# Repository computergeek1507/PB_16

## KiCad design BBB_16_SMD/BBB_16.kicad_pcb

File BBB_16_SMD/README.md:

# Copyright and Disclaimer
Copyright: Scott Hanson

This documentation describes Open Hardware and is licensed under the CERN Open Hardware License Version 2 - Strongly Reciprocal. (CERN-OHL-S)

You may redistribute and modify this documentation under the terms of the CERN OHL-S-v2 (https://ohwr.org/cern_ohl_s_v2.txt). This documentation is distributed WITHOUT ANY EXPRESS OR IMPLIED WARRANTY, INCLUDING OF MERCHANTABILITY, SATISFACTORY QUALITY AND FITNESS FOR A PARTICULAR PURPOSE. Please see the CERN OHL v2-S for applicable conditions

**Under CERN OHL-S-v2, derivative work must be publicly released as defined in subsection 3.3**

# BBB 16 SMD

**WIP** Proceed at your own risk.

The BBB 16 SMD is a Surface Mount(SMD) BeagleBone Version with 16 pixel ports, 1 remote differential port, 2 serial ports, and an expansion header for additional 16 pixel outputs. Uses Falcon v4 (24 pin) Expansion Pinout.

**Warning** Due to part shortages, I have switched this design(v3) to use 3.81mm Phoenix Connectors for the string ports. Most other controllers (Falcon, Kulps) use 3.50mm Phoenix Connectors and the plugs are not compatible. The PCB footprints can accept both 3.81mm and 3.50mm headers, but the parts in the BOM are 3.81mm at the moment. 

To order PCBs upload the ["GERBER-BBB_16.zip"](https://github.com/computergeek1507/PB_16/raw/master/BBB_16_SMD/jlcpcb/gerber/GERBER-BBB_16.zip) file in the "jlcpcb\gerber" folder to jlcpcb.com. Enable the SMD service, 'BOM-BBB_16.csv' is the SMD BOM and 'POS-BBB_16.csv' is the SMD CPL position file.

## [Interactive BOM](https://computergeek1507.github.io/PB_16/BBB_16_SMD/bom/ibom)

## [Part BOM](https://github.com/computergeek1507/PB_16/raw/master/BBB_16_SMD/BBB_16_BOM.ods)

---
## Changelog

v2.1
-
* Switched String Ports to 3.81mm Phoenix Connectors.
* Switched Serial Ports AM26C31 serial chip, same as differential port.
* Updated 5V regulator to "Universal" footprint to support different regulators.

v2
-
* first SMD version.

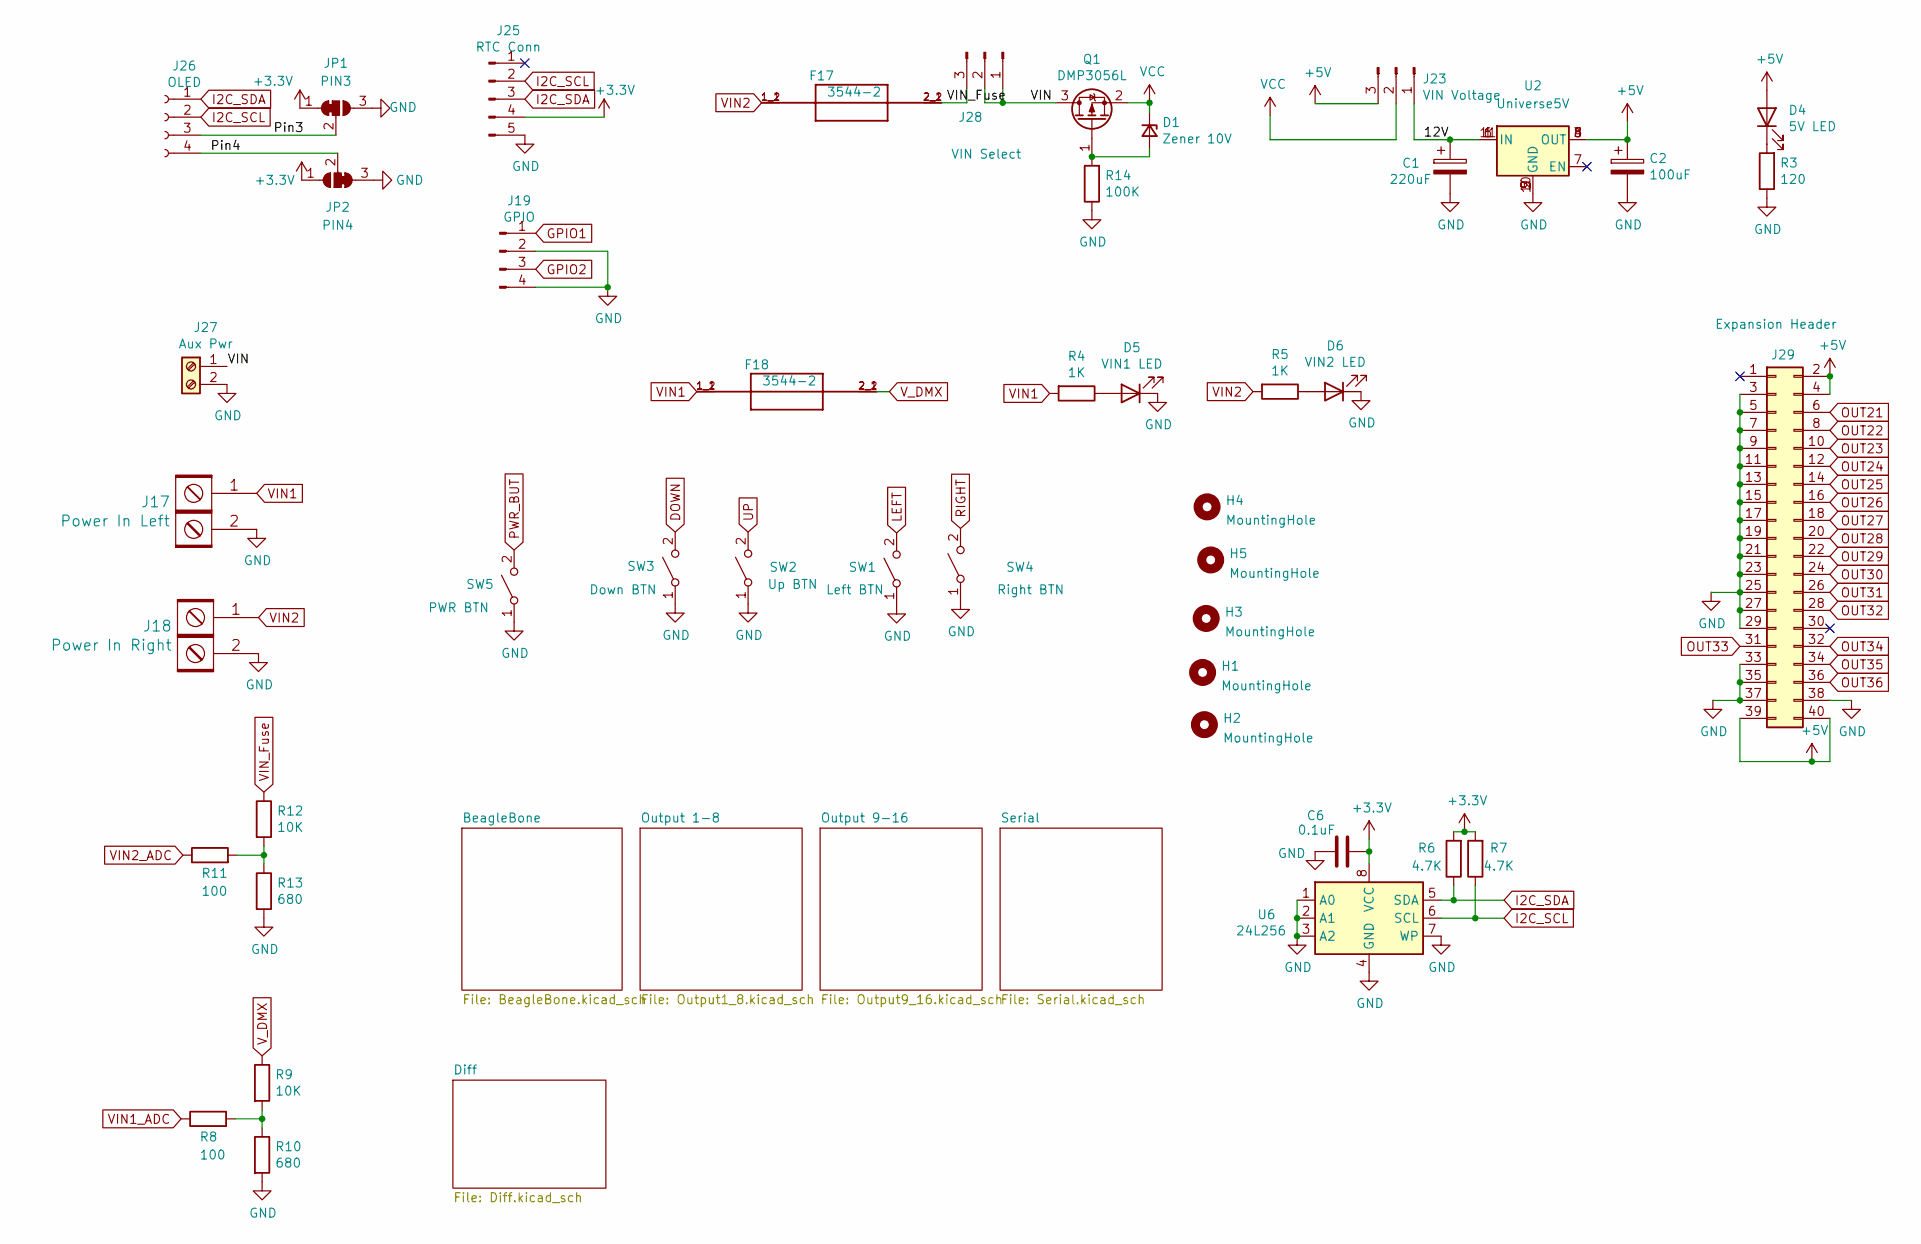
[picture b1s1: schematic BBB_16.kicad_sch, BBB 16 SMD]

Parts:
C1: 220uF; CP_Radial_D10.0mm_P5.00mm; MPN ECA-1HM221; Digi-Key_PN P5183-ND
C2: 100uF; CP_Elec_6.3x5.4_Nichicon; MPN UWX1C101MCL1GB; Digi-Key_PN 493-2105-1-ND
C6: 0.1uF; C_0603_1608Metric_Pad1.08x0.95mm_HandSolder; MPN CL10B104KB8NNWC; Digi-Key_PN 1276-1935-2-ND
D1: Zener 10V; D_SOD-123; MPN MMSZ5240B-7-F; Digi-Key_PN MMSZ5240B-FDICT-ND
D4: 5V LED; LED_0603_1608Metric_Pad1.05x0.95mm_HandSolder; MPN LTST-C190KRKT; Digi-Key_PN 160-1436-2-ND
D5: VIN1 LED; LED_0603_1608Metric_Pad1.05x0.95mm_HandSolder; MPN LTST-C190KRKT; Digi-Key_PN 160-1436-2-ND
D6: VIN2 LED; LED_0603_1608Metric_Pad1.05x0.95mm_HandSolder; MPN LTST-C190KRKT; Digi-Key_PN 160-1436-2-ND
F17, F18: 3544-2; FUSE_3544-2; MPN 3544-2; Digi-Key_PN 36-3544-2-ND
H1, H2, H3, H4, H5: MountingHole; MountingHole_3.7mm
J17: Power In Left; BARRIER_BLOCK_1ROW_2POS_P9.5MM; MPN OSTYK51102030; Digi-Key_PN ED2953-ND
J18: Power In Right; BARRIER_BLOCK_1ROW_2POS_P9.5MM; MPN OSTYK51102030; Digi-Key_PN ED2953-ND
J19: GPIO; JST_XH_B4B-XH-A_1x04_P2.50mm_Vertical; MPN B4B-XH-A(LF)(SN); Digi-Key_PN 455-2249-ND
J23: VIN Voltage; PinHeader_1x03_P2.54mm_Vertical; MPN 61300311121; Digi-Key_PN 732-5316-ND
J25: RTC Conn; PinHeader_1x05_P2.54mm_Vertical; MPN 61300511121; Digi-Key_PN 732-5318-ND
J26: OLED; OLED-SSD1306-128X64-I2C-THT_2HOLE; MPN PPTC041LFBN-RC; Digi-Key_PN S7002-ND
J27: Aux Pwr; PHOENIX_MKDS1_2-3.81; MPN 1727010; Digi-Key_PN 277-1947-ND
J28: VIN Select; PinHeader_1x03_P2.54mm_Vertical; MPN 61300311121; Digi-Key_PN 732-5316-ND
J29: Expansion Header; IDC-Header_2x20_P2.54mm_Vertical; MPN SBH11-PBPC-D20-ST-BK; Digi-Key_PN S9175-ND
JP1: PIN3; SolderJumper-3_P1mm_Bridged12
JP2: PIN4; SolderJumper-3_P1mm_Bridged23
Q1: DMP3056L; SOT-23; MPN DMP3056L-7; Digi-Key_PN DMP3056L-7DICT-ND
R3: 120; R_0603_1608Metric_Pad0.98x0.95mm_HandSolder; MPN CRGCQ0603F120R; Digi-Key_PN A129677CT-ND
R4, R5: 1K; R_0603_1608Metric_Pad0.98x0.95mm_HandSolder; MPN RC0603FR-071KL; Digi-Key_PN 311-1.00KHRTR-ND
R6, R7: 4.7K; R_0603_1608Metric_Pad0.98x0.95mm_HandSolder; MPN RC0603JR-074K7L; Digi-Key_PN 311-4.7KGRCT-ND
R8, R11: 100; R_0603_1608Metric_Pad0.98x0.95mm_HandSolder; MPN RMCF0603FT100R; Digi-Key_PN RMCF0603FT100RCT-ND
R9, R12: 10K; R_0603_1608Metric_Pad0.98x0.95mm_HandSolder; MPN RC0603FR-0710KL; Digi-Key_PN 311-10.0KHRCT-ND
R10, R13: 680; R_0603_1608Metric_Pad0.98x0.95mm_HandSolder; MPN RC0603FR-07680RL; Digi-Key_PN 311-680HRCT-ND
R14: 100K; R_0603_1608Metric_Pad0.98x0.95mm_HandSolder; MPN RT0603BRD07100KL; Digi-Key_PN YAG1235CT-ND
SW1: Left BTN; SW_Push_1P1T_NO_6x6mm_H9.5mm; MPN PTS645SL50SMTR92 LFS; Digi-Key_PN CKN9088CT-ND
SW2: Up BTN; SW_Push_1P1T_NO_6x6mm_H9.5mm; MPN PTS645SL50SMTR92 LFS; Digi-Key_PN CKN9088CT-ND
SW3: Down BTN; SW_Push_1P1T_NO_6x6mm_H9.5mm; MPN PTS645SL50SMTR92 LFS; Digi-Key_PN CKN9088CT-ND
SW4: Right BTN; SW_Push_1P1T_NO_6x6mm_H9.5mm; MPN PTS645SL50SMTR92 LFS; Digi-Key_PN CKN9088CT-ND
SW5: PWR BTN; SW_Push_1P1T_NO_6x6mm_H9.5mm; MPN PTS645SL50SMTR92 LFS; Digi-Key_PN CKN9088CT-ND
U2: Universe5V; Universal_5V_Horizontal
U6: 24L256; SOIC-8_3.9x4.9mm_P1.27mm; MPN 24LC256T-I/MS; Digi-Key_PN 24LC256T-I/MSCT-ND

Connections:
+3V3: C6.1, J25.4, JP1.1 (A), JP2.1 (A), R6.2, R7.2, U6.8 (VCC); also elsewhere on the board
+5V: C2.1, D4.2 (A), J23.3, J29.2, J29.4, J29.39, J29.40, U2.3 (OUT), U2.4 (OUT), U2.8 (OUT); also elsewhere on the board
/12V: C1.1, J23.1, U2.1 (IN), U2.6 (IN), U2.11 (IN)
/Pin3: J26.3, JP1.2 (C)
/Pin4: J26.4, JP2.2 (C)
/VIN: J27.1, J28.1, J28.2, Q1.3 (D)
DOWN: SW3.2 (B); also elsewhere on the board
GND: C1.2, C2.2, C6.2, D5.1 (K), D6.1 (K), J17.2, J18.2, J19.2, J19.4, J25.5, J27.2, J29.3, J29.5, J29.7, J29.9, J29.11, J29.13, J29.15, J29.17, J29.19, J29.21, J29.23, J29.25, J29.27, J29.29, J29.33, J29.35, J29.37, J29.38, JP1.3 (B), JP2.3 (B), R3.1, R10.2, R13.2, R14.1, SW1.1 (A), SW2.1 (A), SW3.1 (A), SW4.1 (A), SW5.1 (A), U2.2 (GND), U2.5 (GND), U2.9 (GND), U2.10 (GND), U6.1 (A0), U6.2 (A1), U6.3 (A2), U6.4 (GND), U6.7 (WP); also elsewhere on the board
GPIO1: J19.1; also elsewhere on the board
GPIO2: J19.3; also elsewhere on the board
I2C_SCL: J25.2, J26.2, R7.1, U6.6 (SCL); also elsewhere on the board
I2C_SDA: J25.3, J26.1, R6.1, U6.5 (SDA); also elsewhere on the board
LEFT: SW1.2 (B); also elsewhere on the board
unnamed: D1.2 (A), Q1.1 (G), R14.2
unnamed: D4.1 (K), R3.2
unnamed: D5.2 (A), R4.1
unnamed: D6.2 (A), R5.1
unnamed: R8.2, R9.2, R10.1
unnamed: R11.2, R12.2, R13.1
OUT21: J29.6; also elsewhere on the board
OUT22: J29.8; also elsewhere on the board
OUT23: J29.10; also elsewhere on the board
OUT24: J29.12; also elsewhere on the board
OUT25: J29.14; also elsewhere on the board
OUT26: J29.16; also elsewhere on the board
OUT27: J29.18; also elsewhere on the board
OUT28: J29.20; also elsewhere on the board
OUT29: J29.22; also elsewhere on the board
OUT30: J29.24; also elsewhere on the board
OUT31: J29.26; also elsewhere on the board
OUT32: J29.28; also elsewhere on the board
OUT33: J29.31; also elsewhere on the board
OUT34: J29.32; also elsewhere on the board
OUT35: J29.34; also elsewhere on the board
OUT36: J29.36; also elsewhere on the board
PWR_BUT: SW5.2 (B); also elsewhere on the board
RIGHT: SW4.2 (B); also elsewhere on the board
UP: SW2.2 (B); also elsewhere on the board
VCC: D1.1 (K), J23.2, Q1.2 (S)
VIN1: F18.1_1 (1), F18.1_2 (1), J17.1, R4.2; also elsewhere on the board
VIN1_ADC: R8.1; also elsewhere on the board
VIN2: F17.1_1 (1), F17.1_2 (1), J18.1, R5.2; also elsewhere on the board
VIN2_ADC: R11.1; also elsewhere on the board
VIN_Fuse: F17.2_1 (2), F17.2_2 (2), J28.3, R12.1
V_DMX: F18.2_1 (2), F18.2_2 (2), R9.1; also elsewhere on the board

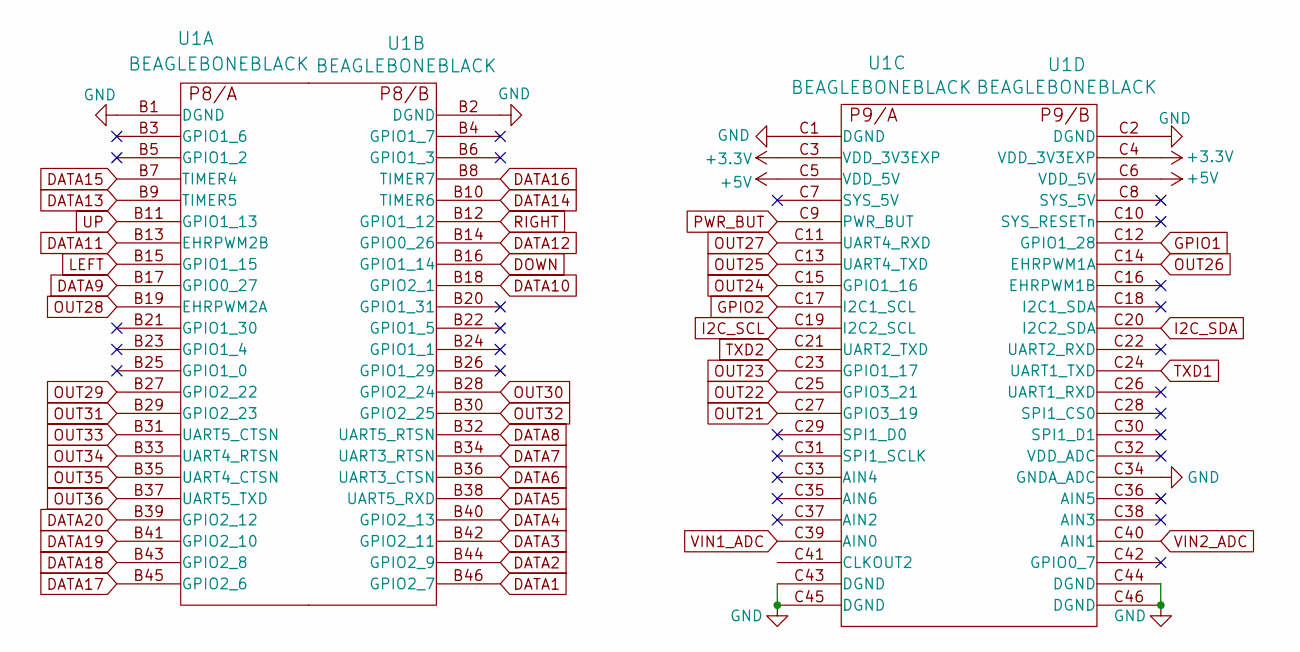
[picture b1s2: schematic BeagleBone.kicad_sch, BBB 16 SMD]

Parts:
U1: BEAGLEBONEBLACK; MPN BBB01-SC-505; Digi-Key_PN BBB01-SC-505-ND

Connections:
+3V3: U1.C3 (VDD_3V3EXP), U1.C4 (VDD_3V3EXP); also elsewhere on the board
+5V: U1.C5 (VDD_5V), U1.C6 (VDD_5V); also elsewhere on the board
DATA1: U1.B46 (GPIO2_7); also elsewhere on the board
DATA2: U1.B44 (GPIO2_9); also elsewhere on the board
DATA3: U1.B42 (GPIO2_11); also elsewhere on the board
DATA4: U1.B40 (GPIO2_13); also elsewhere on the board
DATA5: U1.B38 (UART5_RXD); also elsewhere on the board
DATA6: U1.B36 (UART3_CTSN); also elsewhere on the board
DATA7: U1.B34 (UART3_RTSN); also elsewhere on the board
DATA8: U1.B32 (UART5_RTSN); also elsewhere on the board
DATA9: U1.B17 (GPIO0_27); also elsewhere on the board
DATA10: U1.B18 (GPIO2_1); also elsewhere on the board
DATA11: U1.B13 (EHRPWM2B); also elsewhere on the board
DATA12: U1.B14 (GPIO0_26); also elsewhere on the board
DATA13: U1.B9 (TIMER5); also elsewhere on the board
DATA14: U1.B10 (TIMER6); also elsewhere on the board
DATA15: U1.B7 (TIMER4); also elsewhere on the board
DATA16: U1.B8 (TIMER7); also elsewhere on the board
DATA17: U1.B45 (GPIO2_6); also elsewhere on the board
DATA18: U1.B43 (GPIO2_8); also elsewhere on the board
DATA19: U1.B41 (GPIO2_10); also elsewhere on the board
DATA20: U1.B39 (GPIO2_12); also elsewhere on the board
DOWN: U1.B16 (GPIO1_14); also elsewhere on the board
GND: U1.B1 (DGND), U1.B2 (DGND), U1.C1 (DGND), U1.C2 (DGND), U1.C34 (GNDA_ADC), U1.C43 (DGND), U1.C44 (DGND), U1.C45 (DGND), U1.C46 (DGND); also elsewhere on the board
GPIO1: U1.C12 (GPIO1_28); also elsewhere on the board
GPIO2: U1.C17 (I2C1_SCL); also elsewhere on the board
I2C_SCL: U1.C19 (I2C2_SCL); also elsewhere on the board
I2C_SDA: U1.C20 (I2C2_SDA); also elsewhere on the board
LEFT: U1.B15 (GPIO1_15); also elsewhere on the board
OUT21: U1.C27 (GPIO3_19); also elsewhere on the board
OUT22: U1.C25 (GPIO3_21); also elsewhere on the board
OUT23: U1.C23 (GPIO1_17); also elsewhere on the board
OUT24: U1.C15 (GPIO1_16); also elsewhere on the board
OUT25: U1.C13 (UART4_TXD); also elsewhere on the board
OUT26: U1.C14 (EHRPWM1A); also elsewhere on the board
OUT27: U1.C11 (UART4_RXD); also elsewhere on the board
OUT28: U1.B19 (EHRPWM2A); also elsewhere on the board
OUT29: U1.B27 (GPIO2_22); also elsewhere on the board
OUT30: U1.B28 (GPIO2_24); also elsewhere on the board
OUT31: U1.B29 (GPIO2_23); also elsewhere on the board
OUT32: U1.B30 (GPIO2_25); also elsewhere on the board
OUT33: U1.B31 (UART5_CTSN); also elsewhere on the board
OUT34: U1.B33 (UART4_RTSN); also elsewhere on the board
OUT35: U1.B35 (UART4_CTSN); also elsewhere on the board
OUT36: U1.B37 (UART5_TXD); also elsewhere on the board
PWR_BUT: U1.C9 (PWR_BUT); also elsewhere on the board
RIGHT: U1.B12 (GPIO1_12); also elsewhere on the board
TXD1: U1.C24 (UART1_TXD); also elsewhere on the board
TXD2: U1.C21 (UART2_TXD); also elsewhere on the board
UP: U1.B11 (GPIO1_13); also elsewhere on the board
VIN1_ADC: U1.C39 (AIN0); also elsewhere on the board
VIN2_ADC: U1.C40 (AIN1); also elsewhere on the board

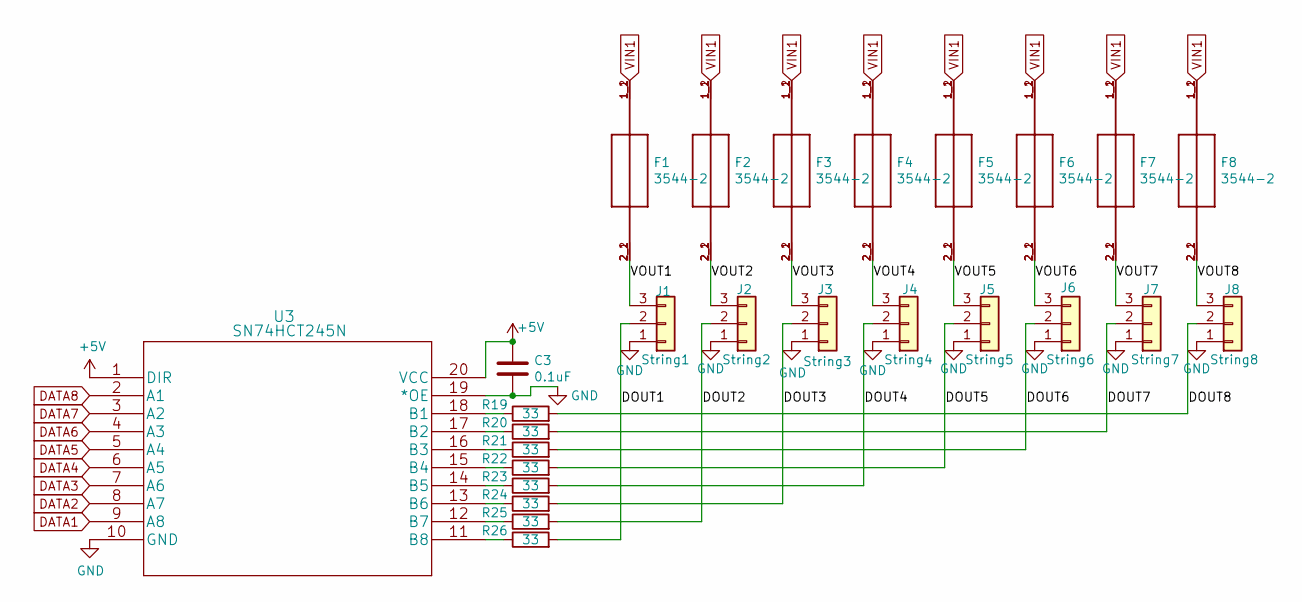
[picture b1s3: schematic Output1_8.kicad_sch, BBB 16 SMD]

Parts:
C3: 0.1uF; C_0603_1608Metric_Pad1.08x0.95mm_HandSolder; MPN CL10B104KB8NNWC; Digi-Key_PN 1276-1935-2-ND
F1, F2, F3, F4, F5, F6, F7, F8: 3544-2; FUSE_3544-2; MPN 3544-2; Digi-Key_PN 36-3544-2-ND
J1: String1; PhoenixContact_MCV_3.81mm_3.5mm_1x03_Vertical; MPN 1843619/OSTTJ0311530; Digi-Key_PN 277-5737-ND/ED10555-ND
J2: String2; PhoenixContact_MCV_3.81mm_3.5mm_1x03_Vertical; MPN 1843619/OSTTJ0311530; Digi-Key_PN 277-5737-ND/ED10555-ND
J3: String3; PhoenixContact_MCV_3.81mm_3.5mm_1x03_Vertical; MPN 1843619/OSTTJ0311530; Digi-Key_PN 277-5737-ND/ED10555-ND
J4: String4; PhoenixContact_MCV_3.81mm_3.5mm_1x03_Vertical; MPN 1843619/OSTTJ0311530; Digi-Key_PN 277-5737-ND/ED10555-ND
J5: String5; PhoenixContact_MCV_3.81mm_3.5mm_1x03_Vertical; MPN 1843619/OSTTJ0311530; Digi-Key_PN 277-5737-ND/ED10555-ND
J6: String6; PhoenixContact_MCV_3.81mm_3.5mm_1x03_Vertical; MPN 1843619/OSTTJ0311530; Digi-Key_PN 277-5737-ND/ED10555-ND
J7: String7; PhoenixContact_MCV_3.81mm_3.5mm_1x03_Vertical; MPN 1843619/OSTTJ0311530; Digi-Key_PN 277-5737-ND/ED10555-ND
J8: String8; PhoenixContact_MCV_3.81mm_3.5mm_1x03_Vertical; MPN 1843619/OSTTJ0311530; Digi-Key_PN 277-5737-ND/ED10555-ND
R19, R20, R21, R22, R23, R24, R25, R26: 33; R_0603_1608Metric_Pad0.98x0.95mm_HandSolder; MPN CN34J330CT; LCSC C23140
U3: SN74HCT245N; SN74HCT245NSR; MPN SN74HC245PWR; Digi-Key_PN 296-8279-1-ND

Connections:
+5V: C3.1, U3.1 (DIR), U3.20 (VCC); also elsewhere on the board
/Output 1-8/DOUT1: J1.2, R26.2
/Output 1-8/DOUT2: J2.2, R25.2
/Output 1-8/DOUT3: J3.2, R24.2
/Output 1-8/DOUT4: J4.2, R23.2
/Output 1-8/DOUT5: J5.2, R22.2
/Output 1-8/DOUT6: J6.2, R21.2
/Output 1-8/DOUT7: J7.2, R20.2
/Output 1-8/DOUT8: J8.2, R19.2
/Output 1-8/VOUT1: F1.2_1 (2), F1.2_2 (2), J1.3
/Output 1-8/VOUT2: F2.2_1 (2), F2.2_2 (2), J2.3
/Output 1-8/VOUT3: F3.2_1 (2), F3.2_2 (2), J3.3
/Output 1-8/VOUT4: F4.2_1 (2), F4.2_2 (2), J4.3
/Output 1-8/VOUT5: F5.2_1 (2), F5.2_2 (2), J5.3
/Output 1-8/VOUT6: F6.2_1 (2), F6.2_2 (2), J6.3
/Output 1-8/VOUT7: F7.2_1 (2), F7.2_2 (2), J7.3
/Output 1-8/VOUT8: F8.2_1 (2), F8.2_2 (2), J8.3
DATA1: U3.9 (A8); also elsewhere on the board
DATA2: U3.8 (A7); also elsewhere on the board
DATA3: U3.7 (A6); also elsewhere on the board
DATA4: U3.6 (A5); also elsewhere on the board
DATA5: U3.5 (A4); also elsewhere on the board
DATA6: U3.4 (A3); also elsewhere on the board
DATA7: U3.3 (A2); also elsewhere on the board
DATA8: U3.2 (A1); also elsewhere on the board
GND: C3.2, J1.1, J2.1, J3.1, J4.1, J5.1, J6.1, J7.1, J8.1, U3.10 (GND), U3.19 (*OE); also elsewhere on the board
unnamed: R19.1, U3.18 (B1)
unnamed: R20.1, U3.17 (B2)
unnamed: R21.1, U3.16 (B3)
unnamed: R22.1, U3.15 (B4)
unnamed: R23.1, U3.14 (B5)
unnamed: R24.1, U3.13 (B6)
unnamed: R25.1, U3.12 (B7)
unnamed: R26.1, U3.11 (B8)
VIN1: F1.1_1 (1), F1.1_2 (1), F2.1_1 (1), F2.1_2 (1), F3.1_1 (1), F3.1_2 (1), F4.1_1 (1), F4.1_2 (1), F5.1_1 (1), F5.1_2 (1), F6.1_1 (1), F6.1_2 (1), F7.1_1 (1), F7.1_2 (1), F8.1_1 (1), F8.1_2 (1); also elsewhere on the board

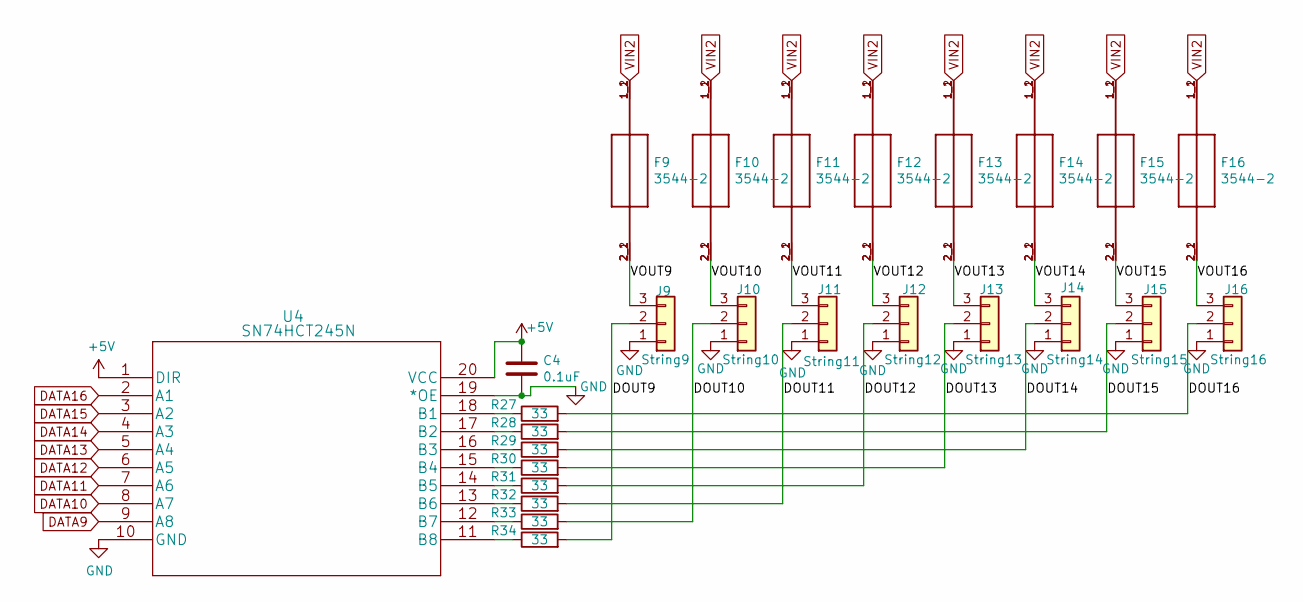
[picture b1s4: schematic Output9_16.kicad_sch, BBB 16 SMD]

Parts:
C4: 0.1uF; C_0603_1608Metric_Pad1.08x0.95mm_HandSolder; MPN CL10B104KB8NNWC; Digi-Key_PN 1276-1935-2-ND
F9, F10, F11, F12, F13, F14, F15, F16: 3544-2; FUSE_3544-2; MPN 3544-2; Digi-Key_PN 36-3544-2-ND
J9: String9; PhoenixContact_MCV_3.81mm_3.5mm_1x03_Vertical; MPN 1843619/OSTTJ0311530; Digi-Key_PN 277-5737-ND/ED10555-ND
J10: String10; PhoenixContact_MCV_3.81mm_3.5mm_1x03_Vertical; MPN 1843619/OSTTJ0311530; Digi-Key_PN 277-5737-ND/ED10555-ND
J11: String11; PhoenixContact_MCV_3.81mm_3.5mm_1x03_Vertical; MPN 1843619/OSTTJ0311530; Digi-Key_PN 277-5737-ND/ED10555-ND
J12: String12; PhoenixContact_MCV_3.81mm_3.5mm_1x03_Vertical; MPN 1843619/OSTTJ0311530; Digi-Key_PN 277-5737-ND/ED10555-ND
J13: String13; PhoenixContact_MCV_3.81mm_3.5mm_1x03_Vertical; MPN 1843619/OSTTJ0311530; Digi-Key_PN 277-5737-ND/ED10555-ND
J14: String14; PhoenixContact_MCV_3.81mm_3.5mm_1x03_Vertical; MPN 1843619/OSTTJ0311530; Digi-Key_PN 277-5737-ND/ED10555-ND
J15: String15; PhoenixContact_MCV_3.81mm_3.5mm_1x03_Vertical; MPN 1843619/OSTTJ0311530; Digi-Key_PN 277-5737-ND/ED10555-ND
J16: String16; PhoenixContact_MCV_3.81mm_3.5mm_1x03_Vertical; MPN 1843619/OSTTJ0311530; Digi-Key_PN 277-5737-ND/ED10555-ND
R27, R28, R29, R30, R31, R32, R33, R34: 33; R_0603_1608Metric_Pad0.98x0.95mm_HandSolder; MPN CN34J330CT; LCSC C23140
U4: SN74HCT245N; SN74HCT245NSR; MPN SN74HC245PWR; Digi-Key_PN 296-8279-1-ND

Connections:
+5V: C4.1, U4.1 (DIR), U4.20 (VCC); also elsewhere on the board
/Output 9-16/DOUT9: J9.2, R34.2
/Output 9-16/DOUT10: J10.2, R33.2
/Output 9-16/DOUT11: J11.2, R32.2
/Output 9-16/DOUT12: J12.2, R31.2
/Output 9-16/DOUT13: J13.2, R30.2
/Output 9-16/DOUT14: J14.2, R29.2
/Output 9-16/DOUT15: J15.2, R28.2
/Output 9-16/DOUT16: J16.2, R27.2
/Output 9-16/VOUT9: F9.2_1 (2), F9.2_2 (2), J9.3
/Output 9-16/VOUT10: F10.2_1 (2), F10.2_2 (2), J10.3
/Output 9-16/VOUT11: F11.2_1 (2), F11.2_2 (2), J11.3
/Output 9-16/VOUT12: F12.2_1 (2), F12.2_2 (2), J12.3
/Output 9-16/VOUT13: F13.2_1 (2), F13.2_2 (2), J13.3
/Output 9-16/VOUT14: F14.2_1 (2), F14.2_2 (2), J14.3
/Output 9-16/VOUT15: F15.2_1 (2), F15.2_2 (2), J15.3
/Output 9-16/VOUT16: F16.2_1 (2), F16.2_2 (2), J16.3
DATA9: U4.9 (A8); also elsewhere on the board
DATA10: U4.8 (A7); also elsewhere on the board
DATA11: U4.7 (A6); also elsewhere on the board
DATA12: U4.6 (A5); also elsewhere on the board
DATA13: U4.5 (A4); also elsewhere on the board
DATA14: U4.4 (A3); also elsewhere on the board
DATA15: U4.3 (A2); also elsewhere on the board
DATA16: U4.2 (A1); also elsewhere on the board
GND: C4.2, J9.1, J10.1, J11.1, J12.1, J13.1, J14.1, J15.1, J16.1, U4.10 (GND), U4.19 (*OE); also elsewhere on the board
unnamed: R27.1, U4.18 (B1)
unnamed: R28.1, U4.17 (B2)
unnamed: R29.1, U4.16 (B3)
unnamed: R30.1, U4.15 (B4)
unnamed: R31.1, U4.14 (B5)
unnamed: R32.1, U4.13 (B6)
unnamed: R33.1, U4.12 (B7)
unnamed: R34.1, U4.11 (B8)
VIN2: F9.1_1 (1), F9.1_2 (1), F10.1_1 (1), F10.1_2 (1), F11.1_1 (1), F11.1_2 (1), F12.1_1 (1), F12.1_2 (1), F13.1_1 (1), F13.1_2 (1), F14.1_1 (1), F14.1_2 (1), F15.1_1 (1), F15.1_2 (1), F16.1_1 (1), F16.1_2 (1); also elsewhere on the board

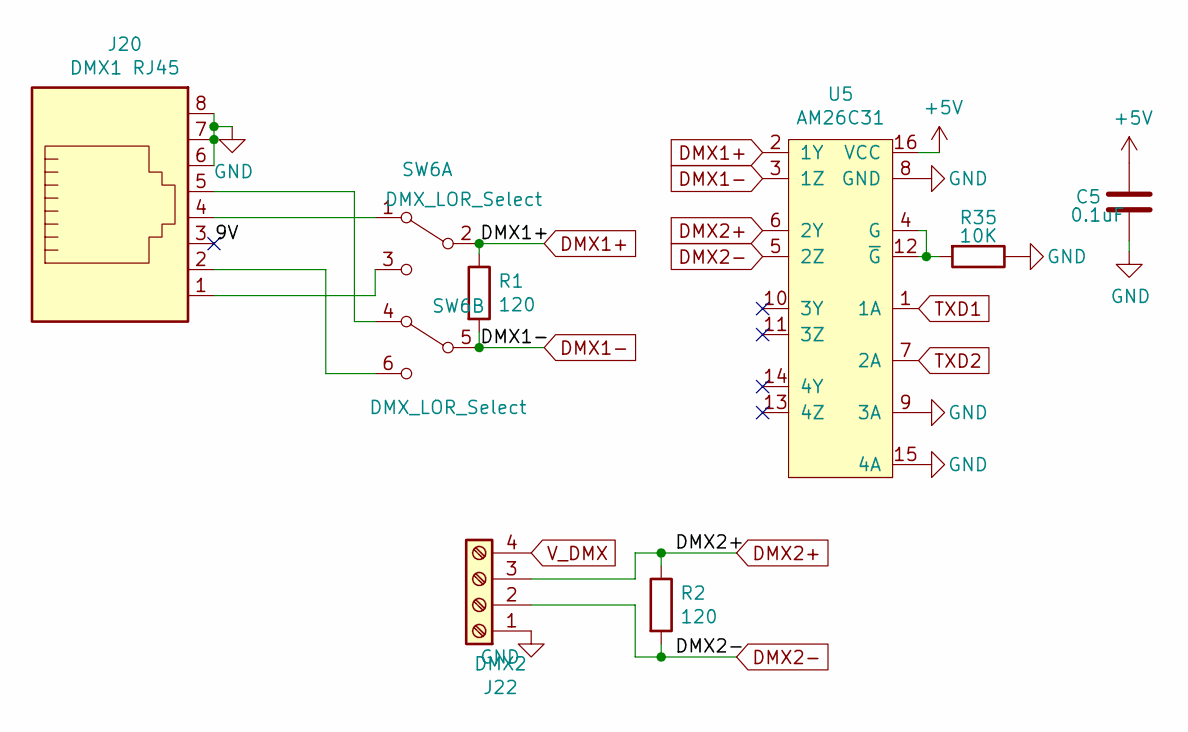
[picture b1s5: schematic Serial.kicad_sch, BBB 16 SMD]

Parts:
C5: 0.1uF; C_0603_1608Metric_Pad1.08x0.95mm_HandSolder; MPN CL10B104KB8NNWC; Digi-Key_PN 1276-1935-2-ND
J20: DMX1 RJ45; RJ45_Amphenol_54602-x08_Horizontal; MPN X05ADIWA1DY1022; Digi-Key_PN AE10392-ND
J22: DMX2; TerminalBlock_Phoenix_MKDS-1,5-4_1x04_P5.00mm_Horizontal; MPN 1729034; Digi-Key_PN 277-1238-ND
R1, R2: 120; R_0603_1608Metric_Pad0.98x0.95mm_HandSolder; MPN CRGCQ0603F120R; Digi-Key_PN A129677CT-ND
R35: 10K; R_0603_1608Metric_Pad0.98x0.95mm_HandSolder; MPN RC0603FR-0710KL; Digi-Key_PN 311-10.0KHRCT-ND
SW6: DMX_LOR_Select; SW_CuK_JS202011CQN_DPDT_Straight; MPN JS202011CQN; Digi-Key_PN 401-2001-ND
U5: AM26C31; SOIC-16_3.9x9.9mm_P1.27mm; MPN AM26C31MDREP; Digikey PN 296-6785-5-ND

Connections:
+5V: C5.1, U5.16 (VCC); also elsewhere on the board
/Serial/9V: J20.3
DMX1+: R1.1, SW6.2 (B), U5.2 (1Y)
DMX1-: R1.2, SW6.5 (B), U5.3 (1Z)
DMX2+: J22.3, R2.1, U5.6 (2Y)
DMX2-: J22.2, R2.2, U5.5 (2Z)
GND: C5.2, J20.6, J20.7, J20.8, J22.1, R35.1, U5.8 (GND), U5.9 (3A), U5.15 (4A); also elsewhere on the board
unnamed: J20.1, SW6.3 (C)
unnamed: J20.2, SW6.6 (C)
unnamed: J20.4, SW6.1 (A)
unnamed: J20.5, SW6.4 (A)
unnamed: R35.2, U5.4 (G), U5.12 (~G)
TXD1: U5.1 (1A); also elsewhere on the board
TXD2: U5.7 (2A); also elsewhere on the board
V_DMX: J22.4; also elsewhere on the board

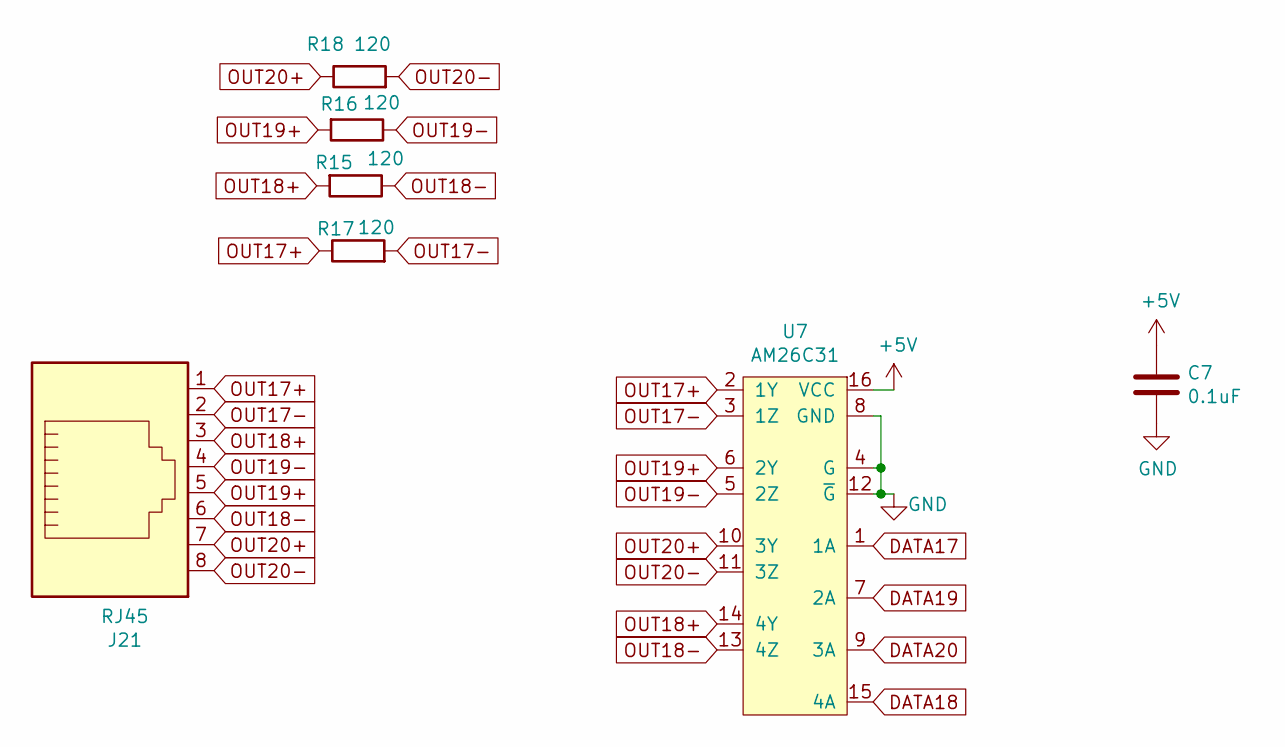
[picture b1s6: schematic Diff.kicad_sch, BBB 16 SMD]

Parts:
C7: 0.1uF; C_0603_1608Metric_Pad1.08x0.95mm_HandSolder; MPN CL10B104KB8NNWC; Digi-Key_PN 1276-1935-2-ND
J21: RJ45; RJ45_Amphenol_54602-x08_Horizontal; MPN X05ADIWA1DY1022; Digi-Key_PN AE10392-ND
R15, R16, R17, R18: 120; R_0603_1608Metric_Pad0.98x0.95mm_HandSolder; MPN CRGCQ0603F120R; Digi-Key_PN A129677CT-ND
U7: AM26C31; SOIC-16_3.9x9.9mm_P1.27mm; MPN AM26C31MDREP; Digikey PN 296-6785-5-ND

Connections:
+5V: C7.1, U7.16 (VCC); also elsewhere on the board
DATA17: U7.1 (1A); also elsewhere on the board
DATA18: U7.15 (4A); also elsewhere on the board
DATA19: U7.7 (2A); also elsewhere on the board
DATA20: U7.9 (3A); also elsewhere on the board
GND: C7.2, U7.4 (G), U7.8 (GND), U7.12 (~G); also elsewhere on the board
OUT17+: J21.1, R17.1, U7.2 (1Y)
OUT17-: J21.2, R17.2, U7.3 (1Z)
OUT18+: J21.3, R15.2, U7.14 (4Y)
OUT18-: J21.6, R15.1, U7.13 (4Z)
OUT19+: J21.5, R16.2, U7.6 (2Y)
OUT19-: J21.4, R16.1, U7.5 (2Z)
OUT20+: J21.7, R18.1, U7.10 (3Y)
OUT20-: J21.8, R18.2, U7.11 (3Z)

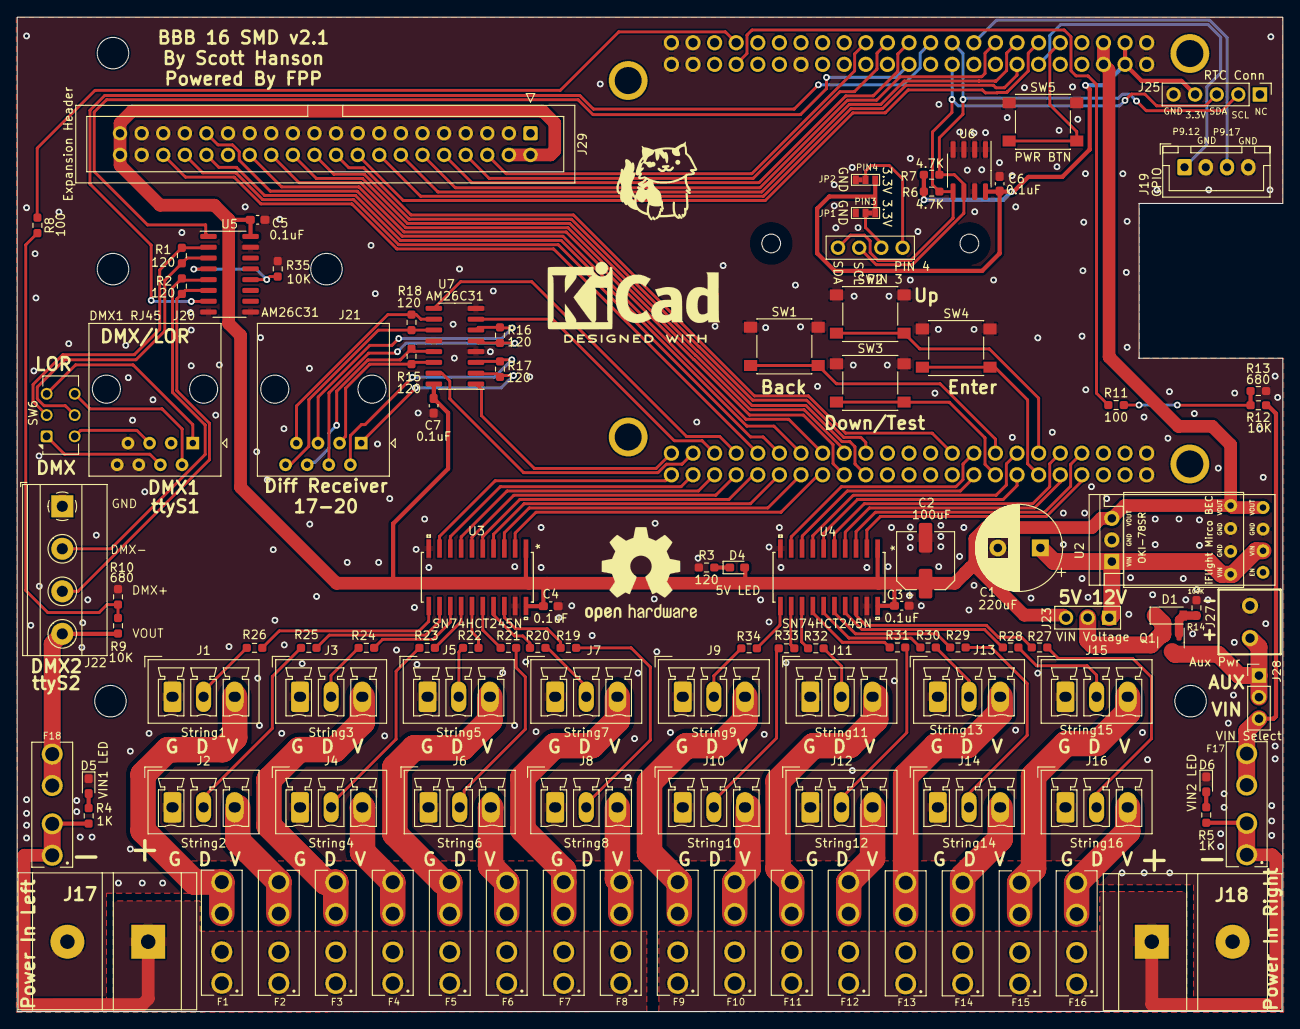
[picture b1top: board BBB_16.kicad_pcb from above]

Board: 2 copper layers, 148.8 x 116.9 mm, 113 parts (0 on the bottom side), 132 nets.

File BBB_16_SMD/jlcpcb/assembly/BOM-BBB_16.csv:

Comment,Designator,Footprint,LCSC
Left BTN,"SW1,SW2,SW3,SW4,SW5",SW_Push_1P1T_NO_6x6mm_H9.5mm,C127509
SN74HCT245N,"U3,U4",SN74HCT245NSR,C133641
100uF,C2,CP_Elec_6.3x5.4_Nichicon,C134723
GPIO,J19,JST_XH_B4B-XH-A_1x04_P2.50mm_Vertical,C144395
0.1uF,"C3,C4,C5,C6,C7",C_0603_1608Metric_Pad1.08x0.95mm_HandSolder,C14663
DMP3056L,Q1,SOT-23,C150724
Zener 10V,D1,D_SOD-123,C173431
120,"R15,R16,R17,R18",R_0603_1608Metric_Pad0.98x0.95mm_HandSolder,C17437
DMX2,J22,"TerminalBlock_Phoenix_MKDS-1,5-4_1x04_P5.00mm_Horizontal",C192769
1K,"R4,R5",R_0603_1608Metric_Pad0.98x0.95mm_HandSolder,C21190
Expansion Header,J24,OST_302-S241,C221083
DMX_LOR_Select,SW6,SW_CuK_JS202011CQN_DPDT_Straight,C221663
OLED,J26,OLED-SSD1306-128X64-I2C-THT_2HOLE,C225501
100,"R11,R8",R_0603_1608Metric_Pad0.98x0.95mm_HandSolder,C22775
120,"R1,R2,R3",R_0603_1608Metric_Pad0.98x0.95mm_HandSolder,C22787
5V LED,"D4,D5,D6",LED_0603_1608Metric_Pad1.05x0.95mm_HandSolder,C2286
33,"R19,R20,R21,R22,R23,R24,R25,R26,R27,R28,R29,R30,R31,R32,R33,R34",R_0603_1608Metric_Pad0.98x0.95mm_HandSolder,C23140
4.7K,"R6,R7",R_0603_1608Metric_Pad0.98x0.95mm_HandSolder,C23162
680,"R10,R13",R_0603_1608Metric_Pad0.98x0.95mm_HandSolder,C23228
100K,R14,R_0603_1608Metric_Pad0.98x0.95mm_HandSolder,C25803
10K,"R12,R35,R9",R_0603_1608Metric_Pad0.98x0.95mm_HandSolder,C25804
DMX1 RJ45,"J20,J21",RJ45_Amphenol_54602-x08_Horizontal,C2938579
AM26C31,"U5,U7",SOIC-16_3.9x9.9mm_P1.27mm,C34923
RTC Conn,J25,PinHeader_1x05_P2.54mm_Vertical,C358687
VIN Voltage,"J23,J28",PinHeader_1x03_P2.54mm_Vertical,C49257
3544-2,"F1,F10,F11,F12,F13,F14,F15,F16,F17,F18,F2,F3,F4,F5,F6,F7,F8,F9",FUSE_3544-2,C492610
24L256,U6,SOIC-8_3.9x4.9mm_P1.27mm,C6482
Aux Pwr,J27,PHOENIX_MKDS1_2-3.81,C69811
Power In Left,"J17,J18",BARRIER_BLOCK_1ROW_2POS_P9.5MM,C707421
String1,"J1,J10,J11,J12,J13,J14,J15,J16,J2,J3,J4,J5,J6,J7,J8,J9",PhoenixContact_MCV_3.81mm_3.5mm_1x03_Vertical,C8389
220uF,C1,CP_Radial_D10.0mm_P5.00mm,C88784
BEAGLEBONEBLACK,U1,BEAGLEBONEBLACK,
Universe5V,U2,Universal_5V_Horizontal,

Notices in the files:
parts and their libraries:
Copyright 2016 Accelerated Designs. All rights reserved.
